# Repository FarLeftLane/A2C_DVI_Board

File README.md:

# A2C_DVI_Board

This is an adapter to let an Apple IIc use an A2DVI card for hdmi video. 4/29/25

**USE AT YOUR OWN RISK.   MIT LICENSE**

This has only been tested with an A2DVI v2 card and a 8BitDevices [A2DVI V3 DVI/HDMI card](https://www.8bitdevices.com/product/a2dvi/).  I don't think the firmware will work on a v4 card, I have one to try.

**BACKGROUND**

I have been working on a project using an ESP32-C6 to take the digital video signals from the Apple IIc DB15 video connector and allow remote viewing of the screen on a PC (watch this account for the ViewIIc plans).   The circuit design was pretty simple, a DB15 connector, a 74VLC245 for level conversion (5V to 3.3V) and a ESP32-C6 module.   It occurred to me that I could take those same Apple IIc signals and using the picoDVI libraries to create an Apple IIc to HDMI solution using an RP2040 or RP2350 (Raspberry Pi Pico).   This is the same HW that is on an A2DVI card for a slotted Apple II (RP2040 and 245's).  I built a Protype ( [A2C_DVI_Prototype](https://github.com/FarLeftLane/A2C_DVI_Prototype) ) that takes the A2DVI card out of a slotted Apple II and instead of connecting to Apple II bus signals (address, data, etc.), we feed the Apple IIc digital video signals into the cards pins and use custom firmware to recreate the display out to HDMI.  This project is a design and PCB for a "production" version of the adapter.

**SCHEMATIC**

[SCHEMATIC](https://github.com/FarLeftLane/A2C_DVI_Board/blob/main/Schematic.pdf)

**ASSEMBLY**

Everything is through-hole, so it is very approachable.  A male 90-deg DB15 connector is used to connect to the Apple IIc.  This connector has to be slightly modified by replacing the male nut screws with two 4/40 3/8" flat head screws you can get at ACE Hardware.  The board has a 50-pin slot for the A2DVI card to plug into, you need to trim the four plastic "feet" off the corners so that it sits flush.  When you solder it in, you don't need to do all 50 pins.  There are white lines near the pins that are required and I would do a few more for structural stability.  The board also has a button/resistors to access the config menu and a 7805 regulator/capacitors to convert +12V from the DB15 to +5V for the card.  You can power the card from a USB connection, but you need a +5V supply to make the config button work.  The +5V pin on the A2DVI card is protected by a diode, so it doesn't produce +5V when you are plugged into USB.  Follow the schematic on how to connect the 7805 and the 2 capacitors to the +12V line.  Solder in the button and the two resistors.  There is a 6 pin header (2x3) that is optional for some additional signals as well as the button signals for a remore button.  8 items, pretty easy.
```
C1 = 0.33uF
C2 = 0.1uF
R1 = 10K
R2 = 1K
```
**SIGNALS**

These are the signals that are routed from the IIc DB15 to the A2DVI card (A2E).

```
PIN_SEROUT  //  A2C Pin 11 - A2E Pin 49
PIN_14M     //  A2C Pin 2  - A2E Pin 48
PIN_WNDW    //  A2C Pin 7  - A2E Pin 47
PIN_TEXT    //  A2C Pin 1  - A2E Pin 46
PIN_GR      //  A2C Pin 10 - A2E Pin 45
PIN_GND     //  A2C Pin 13
PIN_+12V    //  A2C Pin 8

```

**FIRMWARE**

To load the firmware use a USB cable to your PC/Mac with the A2DVI card not slotted into anything.   There is a BOOTSEL button on the pico module.  Hold that button down, and while holding it, plug the USB cable into your PC.   You should see a volume appear on the PC/Mac.  Copy the "A2C_DVI_v1.7.X.uf2" file to this volume and the card should update and reboot.   If you have a HDMI monitor attached to the card, you should see the A2C_DVI splash screen.  Unplug the card from USB.  Never hot-plug the card in the slot or the DB15 connector to the Apple IIc.

[FIRMWARE DOWNLOAD](https://github.com/FarLeftLane/A2C_DVI_Prototype)

**BOM**

You can certainly source these components from places like DigiKey or Mouser for a lot less, but I'm just listing the Amazon links because you can typically get them overnight.

DB15: https://www.amazon.com/dp/B01DLKNHBO

Button: https://www.amazon.com/dp/B07QH9WV12

7805 Regulator and capacitors: https://www.amazon.com/dp/B0BRV3HTXY

Resistors: https://www.amazon.com/dp/B0CDWW5BFH

50-pin slot: https://www.amazon.com/dp/B0BPP5794Z

My boards were fabricated by JLCPCB, $12 for 30 boards and $23 for shipping.  Production files for JLCPCB and the KiCAD designs are included.

**USAGE**

Put your A2DVI card in the slot with the components facing away from the IIc keyboard.  Connect the DB15 directly to the back of the IIc.  Alternately, you can use a [DB15 shielded extension cable](https://www.amazon.com/dp/B09P1LFRB4) if you need to use the Modem serial port.

With the 7805 working, the card should power on when you turn on you IIc.  A short press on the config button will cycle through video modes.  To access the config menu, you make a long press on the button.   Short presses to navigate the menus and long presses to select an option.  Long press on Save to store the settings for subsequent boots.

**ISSUES**

Still working on the color model for the firmware.
Firmware source code will be posted soon.

**COMING SOON?**

I have heard from a couple people that they are designing purpose-built cards based on this design.   Stay tuned...

**SPECIAL THANKS**

- Chris Auger ( https://www.8bitdevices.com/product/a2dvi/ )
- Jonathan Adar
- Jawaid Bazyar
- Ralle Palaveev ( https://github.com/rallepalaveev/A2DVI )
- Thorsten Brehm ( https://github.com/ThorstenBr/A2DVI-Firmware )

**Pictures**

Bare boards:

Assembled board:

Choplifter:

Remember card components face away from keyboard:

Config screen:

DP15 Pinouts

7805 Circuit:

A2C_DVI_Board:

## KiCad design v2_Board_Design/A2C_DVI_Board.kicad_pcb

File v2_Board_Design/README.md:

# A2C_DVI_Board v2: The v2 version is under development and has not been tested yet.  Do not use.

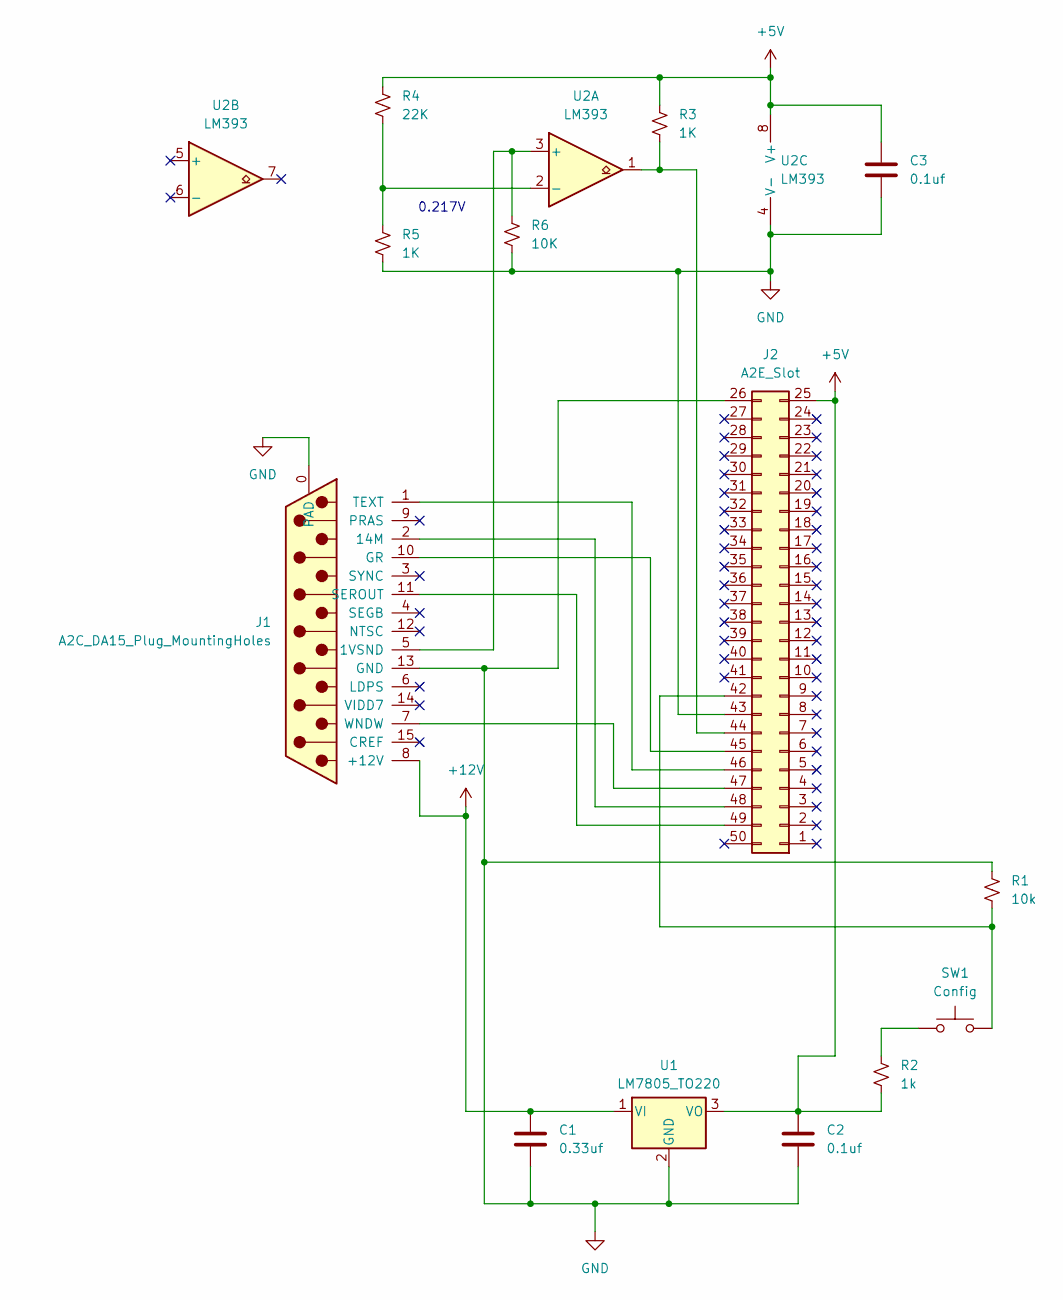
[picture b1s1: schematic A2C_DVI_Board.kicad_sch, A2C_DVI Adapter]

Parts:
C1: 0.33uf; C_Disc_D5.0mm_W2.5mm_P5.00mm
C2, C3: 0.1uf; C_Disc_D5.0mm_W2.5mm_P5.00mm
J1: A2C_DA15_Plug_MountingHoles; DSUB-15_Male_Horizontal_P2.77x2.84mm_EdgePinOffset7.70mm_Ho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
J2: A2E_Slot; A2E_50pin_card_edge_female
R1: 10k; R_Axial_DIN0207_L6.3mm_D2.5mm_P7.62mm_Horizontal
R2: 1k; R_Axial_DIN0207_L6.3mm_D2.5mm_P7.62mm_Horizontal
R3, R5: 1K; R_Axial_DIN0207_L6.3mm_D2.5mm_P7.62mm_Horizontal
R4: 22K; R_Axial_DIN0207_L6.3mm_D2.5mm_P7.62mm_Horizontal
R6: 10K; R_Axial_DIN0207_L6.3mm_D2.5mm_P7.62mm_Horizontal
SW1: Config; PinSocket_1x03_P2.54mm_Vertical
U1: LM7805_TO220; TO-220-3_Vertical
U2: LM393; DIP-8_W7.62mm

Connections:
+5V: C2.1, C3.1, J2.25, R2.2, R3.1, R4.1, U1.3 (VO), U2.8 (V+)
+12V: C1.1, J1.8 (+12V), U1.1 (VI)
GND: C1.2, C2.2, C3.2, J1.0 (PAD), J1.13 (GND), J2.26, J2.43, R1.1, R5.2, R6.2, U1.2 (GND), U2.4 (V-)
unnamed: J1.5 (1VSND), R6.1, U2.3 (+)
unnamed: J1.2 (14M), J2.48
unnamed: J1.10 (GR), J2.45
unnamed: J1.11 (SEROUT), J2.49
unnamed: J1.1 (TEXT), J2.46
unnamed: J1.7 (WNDW), J2.47
unnamed: J2.42, R1.2, SW1.2
unnamed: J2.44, R3.2, U2.1
unnamed: R2.1, SW1.1
unnamed: R4.2, R5.1, U2.2 (-)

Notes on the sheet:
0.217V

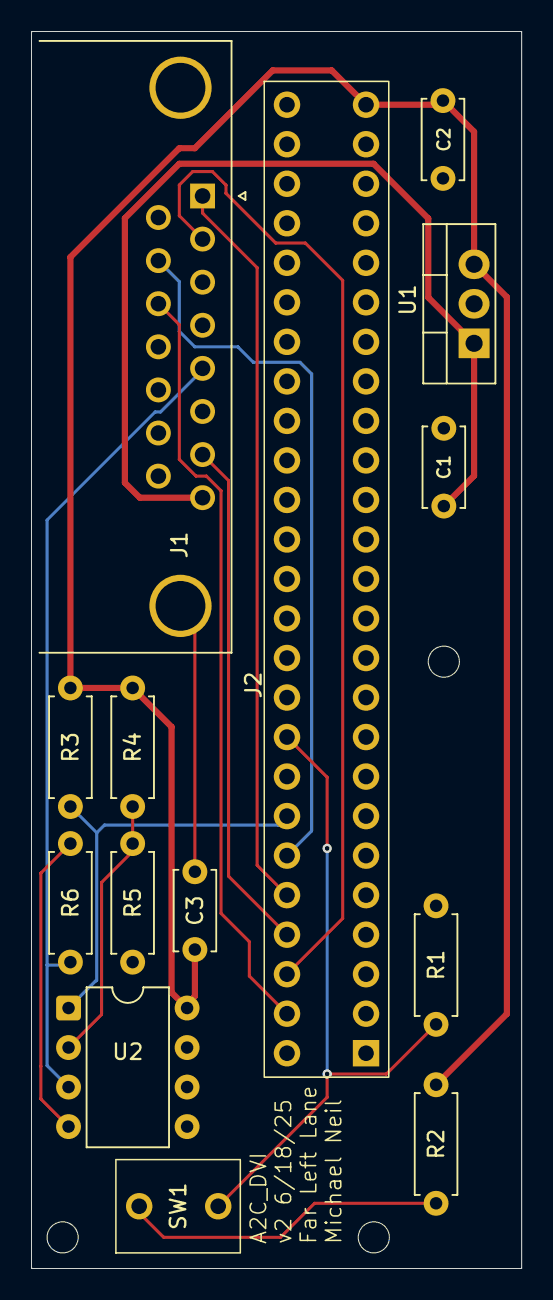
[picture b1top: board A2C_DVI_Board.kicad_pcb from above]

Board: 2 copper layers, 31.5 x 79.5 mm, 14 parts (0 on the bottom side), 13 nets.

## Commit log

2025-04-29 First submit
2025-04-29 Add pdf
2025-06-19 Added pre-release version of the v2 board
2025-06-19 Added README.md for v2
2025-06-19 Added production
